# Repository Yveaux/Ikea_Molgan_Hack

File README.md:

# Ikea Molgan Hack
This project adds wireless functionality and an Arduino Pro-Mini compatible microntroller to an Ikea Molgan LED light with motion sensor.

Original features
========
* Powered from 3 AAA batteries
* Motion PIR sensor, which switches on the LED light for some time when detecting motion.
* Nice, compact enclosure
* Mounting plate
* Cheap, approx. E 4,99

Hacked features
========
* Atmel ATmega328P microntroller, compatible with Arduino Pro-Mini
* nRF24L01+ 2.4GHz radio module (not WiFi!)
* Optional ATSHA204 CryptoAthentication chip
* Default sketch implements a [MySensors][1] enabled motion sensor
* Serial connector for programming sketches
* ISP for programming the ATmega directly
* LED light function can be removed, either partially or complete, to save battery power
* Quite cheap, around E 10,- including Molgan.

The project consists of a custom PCB, which is mounted on top of the original Molgan PCB.
I had the custom PCB produced in white, to prevent it from being visible trhough the semi-transparent cover of the Molgan.

What do you need
========
* Ikea Molgan
* Components, as described in the [BOM][2] (LibreOffice Calc format)
* An In-circuit-programmer to flash the ATmega328, or a pre-flashed ATmega328

Add-on PCB construction
========
To keep the PCB small, it is built with SMD components and thus requires quite some soldering skills to put it all together!
Start by mounting the ATmega328, followed by the other SMD components.
The headers are the only through-hole components used, but the bottom of the resulting add-on PCB should be as flat as possible.
I used a wire clipper to clip the ends off the headers before mounting them, as shown in the following picture (bottom image is after clipping).

Try to insert them without extending below the bottom of the PCB.
Next picture from the side shows how flat it can be.

Finish by soldering the nRF24L01+ SMD module.

Preparing the Molgan
========
Remove the top cover by carefully prying something flat between the bottom and top cover.
Work your way around carefully, without damaging the enclosure. The Molgan's I opened were all glued together with some double sticky tape which makes them harder to open.
With the top cover removed the PCB reveals itself.

Remove the two screws and the blobs of solder als the + and - connection, which connect the PCB to the battery compartiment.
Flip over the PCB.

Now decide if you want to keep the (partial) LED function of the Molgan, or if you turn it into a wireless motion sensor only:
* Resistors R12..R16 are used to power the LEDs at the fron of the PCB. Removing a LED's resitor will effectively disable it.
* Removing resistor R17 disables all LEDs at once.

Solder a small wire to the right pad of R17, which will signal the add-on PCB that motion has been detected.
Make it about as long as on the next picture.

Remove the light sensor on the front (marked 'cds') or the sensor will only detect motion in the dark.
I also replaced R11 by a 120 ohms resistor, to decrease the retrigger time of the PIR to less than a second.

Now drill a small hole next to the battery spring, close to the mounting screw and solder a small wire to the spring base. Use a knife to scratch the surface of the metal a bit or the solder won't stick to it.

Putting it all together
========
Place the Molgan PCB back into the bottom enclosure and fasten only the left screw.
Align the add-on PCB on top of the Molgan PCB, as shown in the picture.

Solder the new power connection from the battery compartment to the + connection of the add-on PCB.
Connect the - on the add-on PCB to the - on the Molgan PCB (I used a small piece of solder wick).
Restore both connections to the batteries.

Flashing the Arduino bootloader
========
This step is required when you acquired a bare ATmega, without Arduino bootlader.
I won't go into details how to do this, as the internet is full of guides, e.g. using an [Arduino][3].

Connect the ISP to the add-on PCB, put some batteries in the Molgan and flash the default Pro-Mini bootloader (called 'ATmegaBOOT_168_atmega328_pro_8MHz.hex') which is part of the Arduino IDE, or can be found [here][4].

Set the fuses to
* EXTENDED: 0xFE
* HIGH: 0xDA
* LOW: 0xE2

Downloading the MySensors motion detector sketch
========
Remove the batteries and connect a standard FTDI serial cable (the ones used to program an Arduino Pro-Mini) to the FTDI connector of the add-on PCB.
Replace the batteries and plug the FTDI cable in your PC.

Start the Arduino IDE and load the [sketch][5].
Change target board to 'Arduino Pro or Pro Mini' and set processor to 'ATmeag328 (3.3V, 8MHz)'.

The sketch will sleep until woken by a motion trigger from the Molgan, or wake up once every 24 hours to check battery level.
It will send a V_TRIPPED message to the gateway and measures the battery level.
For this it uses my [Vcc library][6], whcih should be installed in the IDE.
After a short blind time (set to 30 sec default) the motion sensor is sensitive to triggers again.
This blind time prevents the motion sensor from spamming the gateway with tripped-messages. This time can also be set in hardware (by resistor R11), but software allows for easier tweaking.

The onboard LED is used as a Tx indication by the MySensors library.

Tune the sketch to your liking and upload the sketch.

[1]: https://www.mysensors.org
[2]: https://raw.githubusercontent.com/Yveaux/Ikea_Molgan_Hack/master/pcb/Ikea_Molgan_bom.ods
[3]: https://www.arduino.cc/en/Tutorial/ArduinoISP
[4]: https://github.com/arduino/Arduino/blob/master/hardware/arduino/avr/bootloaders/atmega/ATmegaBOOT_168_atmega328_pro_8MHz.hex
[5]: https://raw.githubusercontent.com/Yveaux/Ikea_Molgan_Hack/master/src/MotionSensor.ino
[6]: https://github.com/Yveaux/Arduino_Vcc

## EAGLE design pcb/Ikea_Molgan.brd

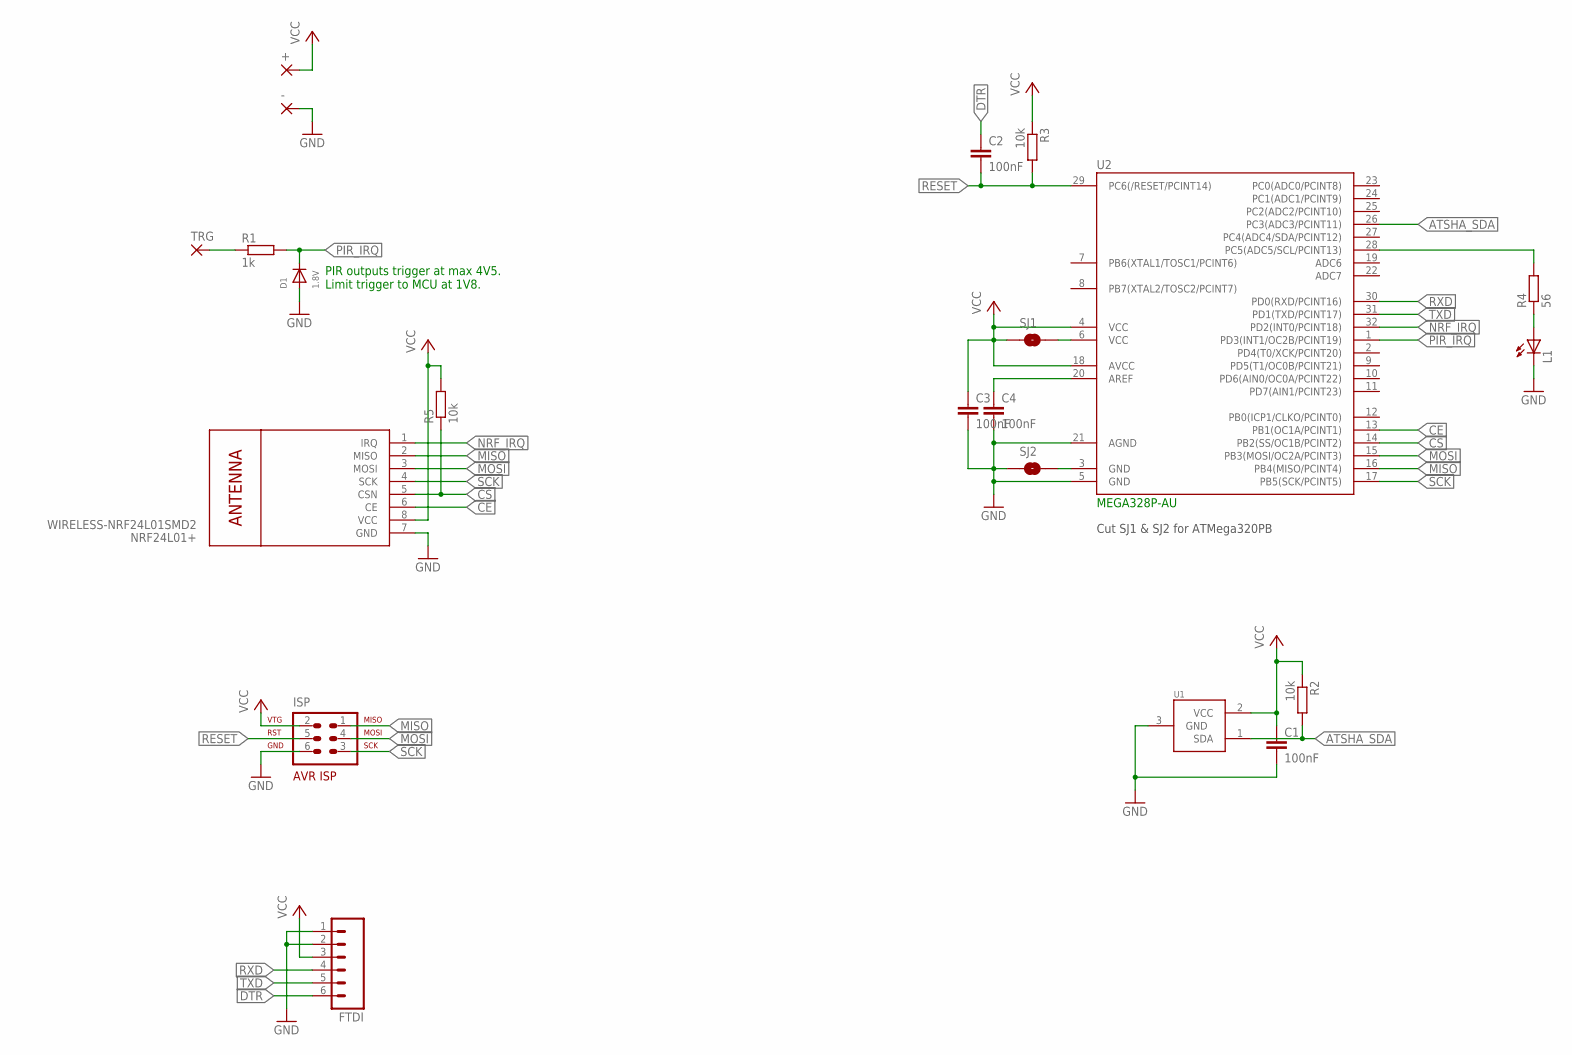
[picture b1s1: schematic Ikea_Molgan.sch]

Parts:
+: WIREPADSMD2,54-5,08; SMD2,54-5,08
-: WIREPADSMD2,54-5,08; SMD2,54-5,08
C1, C2, C3, C4: 100nF; C0805
D1: 1.8V; SOD-123
FTDI: M06SIP; 1X06
ISP: AVR-ISP-6
L1: LEDCHIPLED_0805; CHIPLED_0805
NRF24L01+: WIRELESS-NRF24L01SMD2; WIRELESS-NRF24L01-SMD-2
R1: 1k; R0805
R2, R3, R5: 10k; R0805
R4: 56; R0805
SJ1, SJ2: SOLDERJUMPERTRACE; SJ_2S-TRACE
TRG: WIREPADSMD2,54-5,08; SMD2,54-5,08
U1: IC_ATSHA204A_CRYPT; SOT23-3
U2: MEGA328P-AU; TQFP32-08

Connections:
ATSHA_SDA: R2.2, U1.1 (SDA), U2.26 (PC3(ADC3/PCINT11))
CE: NRF24L01+.6 (CE), U2.13 (PB1(OC1A/PCINT1))
CS: NRF24L01+.5 (CSN), R5.1, U2.14 (PB2(SS/OC1B/PCINT2))
DTR: C2.1, FTDI.6
GND: -.1, C1.2, C3.2, C4.2, D1.A, FTDI.1, FTDI.2, ISP.6, L1.C, NRF24L01+.7 (GND), SJ2.1, U1.3 (GND), U2.5 (GND), U2.21 (AGND)
MISO: ISP.1, NRF24L01+.2 (MISO), U2.16 (PB4(MISO/PCINT4))
MOSI: ISP.4, NRF24L01+.3 (MOSI), U2.15 (PB3(MOSI/OC2A/PCINT3))
unnamed: R1.1, TRG.1
unnamed: L1.A, R4.1
unnamed: R4.2, U2.28 (PC5(ADC5/SCL/PCINT13))
unnamed: SJ1.2, U2.6 (VCC)
unnamed: SJ2.2, U2.3 (GND)
unnamed: C4.1, U2.20 (AREF)
NRF_IRQ: NRF24L01+.1 (IRQ), U2.32 (PD2(INT0/PCINT18))
PIR_IRQ: D1.C, R1.2, U2.1 (PD3(INT1/OC2B/PCINT19))
RESET: C2.2, ISP.5, R3.2, U2.29 (PC6(/RESET/PCINT14))
RXD: FTDI.4, U2.30 (PD0(RXD/PCINT16))
SCK: ISP.3, NRF24L01+.4 (SCK), U2.17 (PB5(SCK/PCINT5))
TXD: FTDI.5, U2.31 (PD1(TXD/PCINT17))
VCC: +.1, C1.1, C3.1, FTDI.3, ISP.2, NRF24L01+.8 (VCC), R2.1, R3.1, R5.2, SJ1.1, U1.2 (VCC), U2.4 (VCC), U2.18 (AVCC)

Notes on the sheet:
PIR outputs trigger at max 4V5. Limit trigger to MCU at 1V8.
Cut SJ1 & SJ2 for ATMega320PB

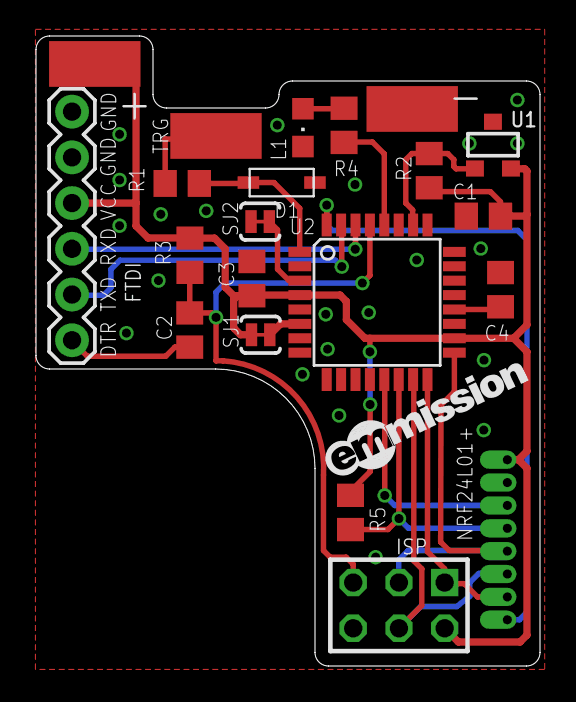
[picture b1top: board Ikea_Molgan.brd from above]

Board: 2 copper layers, 28.0 x 35.0 mm, 22 parts (0 on the bottom side), 20 nets.

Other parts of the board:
U$1: EMMISSION_LOGO_12MM_NOTAG

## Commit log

2016-11-09 Add PCB
2016-11-09 Add images
2016-11-09 Add gerbers
2016-11-10 Added Arduino sketch

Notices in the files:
parts and their libraries:
SparkFun: Licensing: CC v3.0 Share-Alike You are welcome to use this library for commercial purposes.
